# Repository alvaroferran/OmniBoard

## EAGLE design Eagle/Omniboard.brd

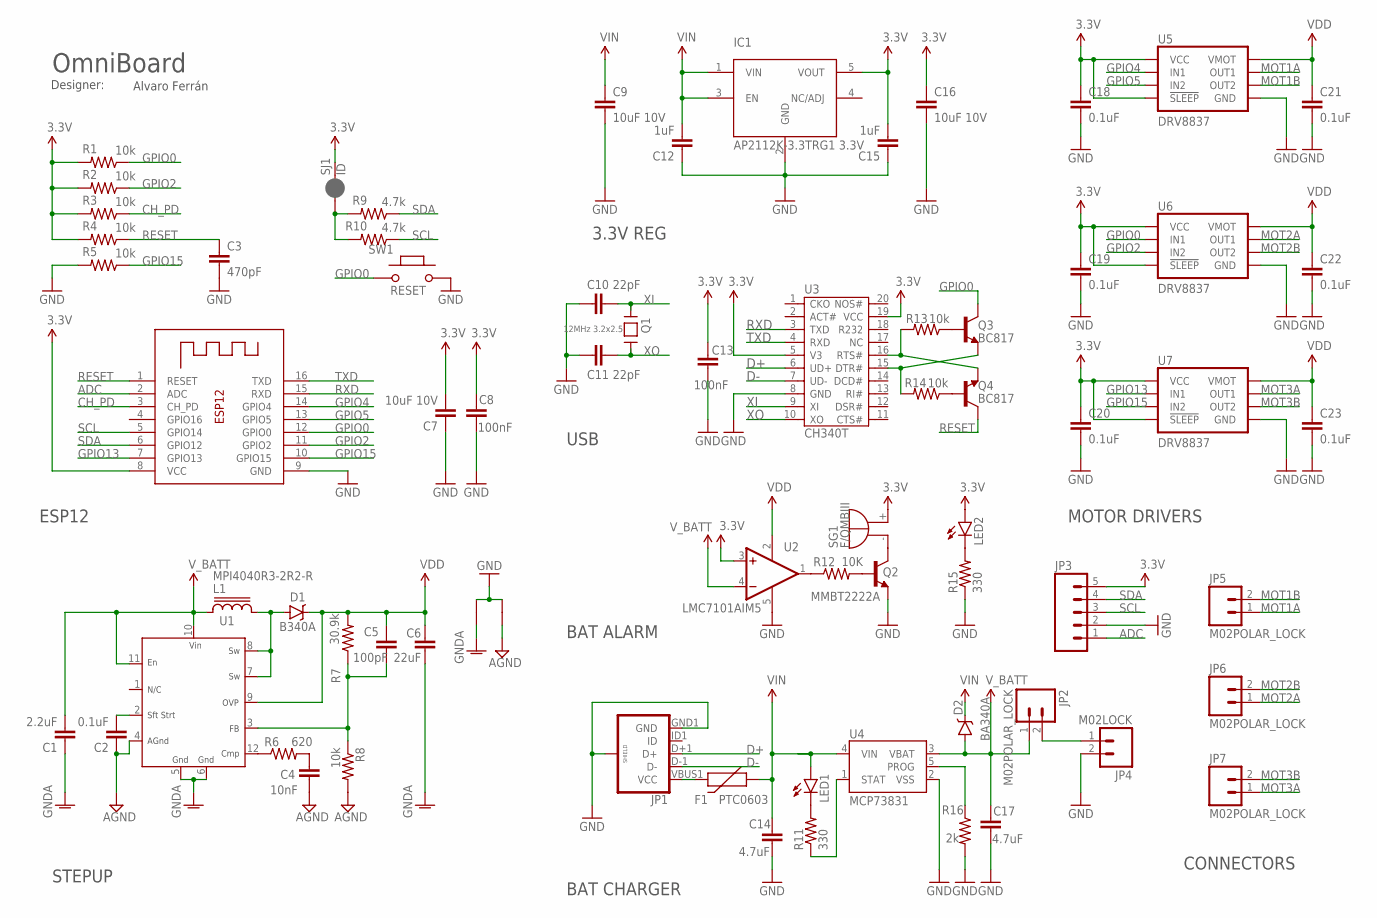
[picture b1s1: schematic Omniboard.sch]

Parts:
C1: 2.2uF; 0603-CAP
C2: 0.1uF; 0603-CAP
C3: 470pF; 0402-CAP
C4: 10nF; 0603-CAP
C5: 100pF; 0603-CAP
C6: 22uF; 0805
C7: 10uF 10V; 0402-CAP
C8, C13: 100nF; 0402-CAP
C9, C16: 10uF 10V; 0603-CAP
C10, C11: 22pF; 0402-CAP
C12, C15: 1uF; 0603-CAP
C14, C17: 4.7uF; 0402-CAP
C18, C19, C20, C21, C22, C23: 0.1uF; 0402-CAP
D1: B340A; SMA-DIODE
D2: BA340A; SMA-DIODE
F1: PTC0603; 0603
GND10, GND13: VIRTUAL_GND; STARGND
IC1: AP2112K-3.3TRG1 3.3V; SOT23-5
JP1: USB_MICROB; USB-B-MICRO-SMD_V03
JP2, JP5, JP6, JP7: M02POLAR_LOCK; MOLEX-1X2_LOCK
JP3: M05LOCK; 1X05_LOCK
JP4: M02LOCK; 1X02_LOCK
L1: MPI4040R3-2R2-R
LED1, LED2: LED0603; LED-0603
Q1: 12MHz 3.2x2.5; CRYSTAL_3.2X2.5
Q2: MMBT2222A; SOT23-3
Q3, Q4: BC817; SOT23-BEC
R1, R2, R3, R4, R5, R13, R14: 10k; R0402
R6: 620; 0603-RES
R7: 30.9k; 0603-RES
R8: 10k; 0603-RES
R9, R10: 4.7k; R0402
R11, R15: 330; 0402-RES
R12: 10K; 0402-RES
R16: 2k; 0402-RES
SG1: F/QMBIII
SJ1: ID; PAD-JUMPER-2-NC_BY_PASTE_YES_SILK
SW1: RESET; 157SW
U1: MIC2253; MLF12_3.0MM_X_3.0MM
U2: LMC7101AIM5; SOT23-5
U3: CH340T; SSOP20
U4: MCP73831; SOT23-5
U5, U6, U7: DRV8837; DSG
X1: ESP-12

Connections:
3.3V: C7.2, C8.1, C13.2, C15.2, C16.1, C18.1, C19.1, C20.1, IC1.5 (VOUT), JP3.5, LED2.A, R1.2, R2.2, R3.2, R4.2, SG1.+ (-), SJ1.2, U2.3 (+IN), U3.5 (V3), U3.19 (VCC), U5.7 (!SLEEP), U5.8 (VCC), U6.7 (!SLEEP), U6.8 (VCC), U7.7 (!SLEEP), U7.8 (VCC), X1.8 (VCC)
ADC: JP3.1, X1.2 (ADC)
AGND: C2.1, C4.1, GND13.P$1, R8.2, U1.4 (AGND)
CH_PD: R3.1, X1.3 (CH_PD)
D+: JP1.D+1 (D+), U3.6 (UD+)
D-: JP1.D-1 (D-), U3.7 (UD-)
GND: C3.2, C7.1, C8.2, C9.2, C10.1, C11.1, C12.1, C13.1, C14.2, C15.1, C16.2, C17.2, C18.2, C19.2, C20.2, C21.2, C22.2, C23.2, GND10.P$2, GND13.P$2, IC1.2 (GND), JP1.GND1 (GND), JP1.SHIELD1 (SHIELD), JP1.SHIELD2 (SHIELD), JP1.SHIELD3 (SHIELD), JP3.2, JP4.2, Q2.2 (E), R5.2, R15.1, R16.2, SW1.2, U2.5 (V-), U3.8 (GND), U4.2 (VSS), U5.4 (GND), U5.PAD (GND), U6.4 (GND), U6.PAD (GND), U7.4 (GND), U7.PAD (GND), X1.9 (GND)
GPIO0: Q3.C, R1.1, SW1.1, U6.6 (IN1), X1.12 (GPIO0)
GPIO2: R2.1, U6.5 (IN2), X1.11 (GPIO2)
GPIO4: U5.6 (IN1), X1.14 (GPIO4)
GPIO5: U5.5 (IN2), X1.13 (GPIO5)
GPIO13: U7.6 (IN1), X1.7 (GPIO13)
GPIO15: R5.1, U7.5 (IN2), X1.10 (GPIO15)
MOT1A: JP5.1, U5.2 (OUT1)
MOT1B: JP5.2, U5.3 (OUT2)
MOT2A: JP6.1, U6.2 (OUT1)
MOT2B: JP6.2, U6.3 (OUT2)
MOT3A: JP7.1, U7.2 (OUT1)
MOT3B: JP7.2, U7.3 (OUT2)
unnamed: R9.2, R10.2, SJ1.1
unnamed: Q3.E, R14.2, U3.15 (DTR#)
unnamed: C4.2, R6.2
unnamed: C2.2, U1.2 (SS)
unnamed: LED1.C, R11.2
unnamed: Q3.B, R13.1
unnamed: Q4.B, R14.1
unnamed: Q2.1 (B), R12.2
unnamed: Q2.3 (C), SG1.- (+)
unnamed: Q4.E, R13.2, U3.16 (RTS#)
unnamed: R16.1, U4.5 (PROG)
unnamed: D1.A, L1.P$2 (2), U1.7 (SW), U1.8 (SW)
unnamed: R11.1, U4.1 (STAT)
unnamed: F1.2, JP1.VBUS1 (VCC)
unnamed: LED2.C, R15.2
unnamed: R6.1, U1.12 (CMP)
unnamed: R12.1, U2.1 (OUT)
unnamed: C5.1, R7.1, R8.1, U1.3 (FB)
PGND: C1.1, C6.1, GND10.P$1, U1.5 (GND), U1.6 (GND)
RESET: C3.1, Q4.C, R4.1, X1.1 (RESET)
RXD: U3.3 (TXD), X1.15 (RXD)
SCL: JP3.3, R10.1, X1.5 (GPIO14)
SDA: JP3.4, R9.1, X1.6 (GPIO12)
TXD: U3.4 (RXD), X1.16 (TXD)
VBAT: JP2.2, JP4.1
VDD: C5.2, C6.2, C21.1, C22.1, C23.1, D1.C, R7.2, U1.9 (OVP), U2.2 (V+), U5.1 (VMOT), U6.1 (VMOT), U7.1 (VMOT)
VIN: C9.1, C12.2, C14.1, D2.C, F1.1, IC1.1 (VIN), IC1.3 (EN), LED1.A, U4.4 (VIN)
V_BATT: C1.2, C17.1, D2.A, JP2.1, L1.P$1 (1), U1.10 (VIN), U1.11 (EN), U2.4 (-IN), U4.3 (VBAT)
XI: C10.2, Q1.3, U3.9 (XI)
XO: C11.2, Q1.1, U3.10 (XO)

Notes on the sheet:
USB
OmniBoard
Designer:
Alvaro Ferrán
3.3V REG
ESP12
MOTOR DRIVERS
BAT ALARM
CONNECTORS
BAT CHARGER
STEPUP

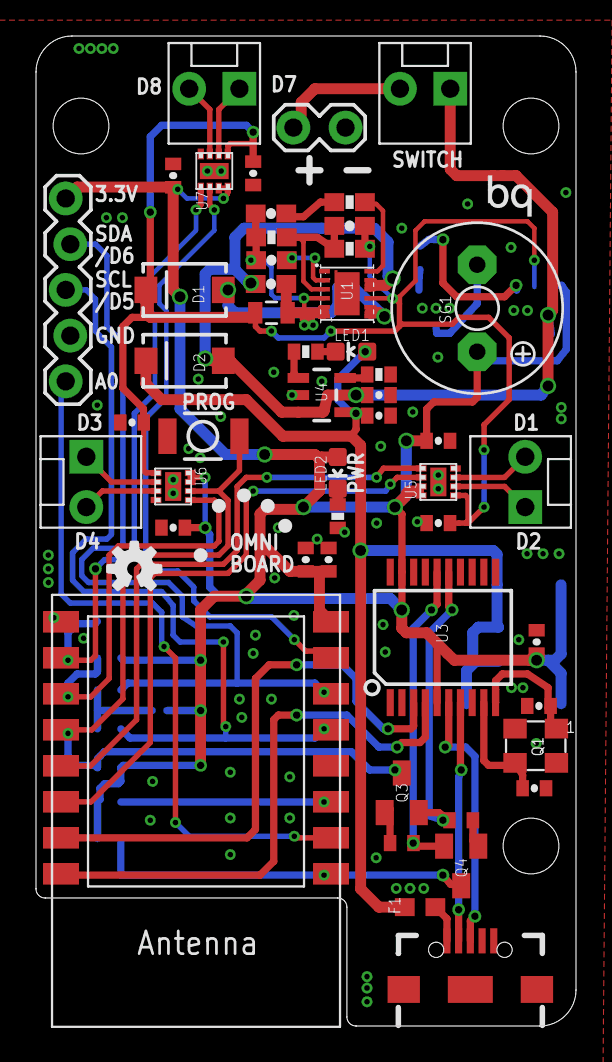
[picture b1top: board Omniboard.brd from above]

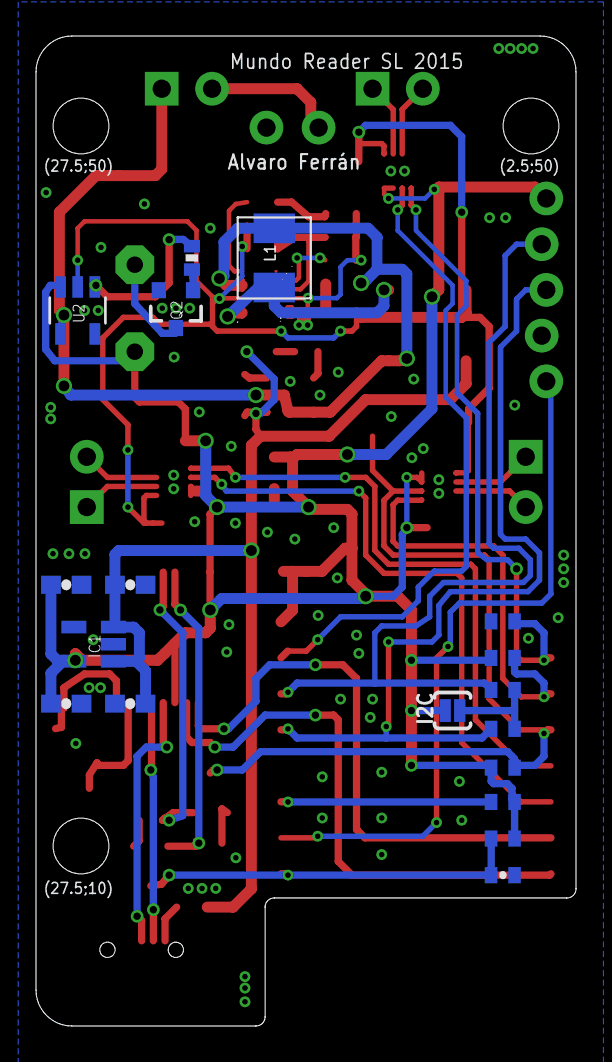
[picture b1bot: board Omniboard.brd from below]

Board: 2 copper layers, 30.0 x 55.0 mm, 73 parts (18 on the bottom side), 49 nets.

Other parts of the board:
U$1: OSHW-LOGO-S
U$3: BQ_LOGO_SMALL_2
U$4: BQ_LOGO_SMALL_1

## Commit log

2015-11-30 Board added
2015-12-22 Changed to 1S lipo, button added, bugs fixed
2016-02-24 Project updated
2016-02-26 Image updated
2016-02-26 Doc added
2016-03-14 json added

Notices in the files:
parts and their libraries:
SparkFun-Passives: Licensing: Creative Commons ShareAlike 4.0 International - https://creativecommons.org/licenses/by-sa/4.0
SparkFun-PowerIC: Licensing: CC v3.0 Share-Alike You are welcome to use this library for commercial purposes.
